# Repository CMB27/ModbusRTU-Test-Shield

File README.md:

# ModbusRTU Test Shield

A shield for Arduino boards that provides an RS-485 transceiver, RS-232 transceiver, and a selection of buttons, lights, and knobs.
This board was designed to aid in testing the [ModbusRTUSlave](https://github.com/CMB27/ModbusRTUSlave) and [ModbusRTUMaster](https://github.com/CMB27/ModbusRTUMaster) libraries.

- This shield is designed to work with both 5V and 3.3V Arduino boards.
- A 3-position removable screw terminal is used as the RS-485 interface.
- A RJ12 connector is used as the RS-232 inteface. The pinout of this connector is designed to make it compatible with Automation Direct products.
- The potentiomter knobs can be easily removed so you can stack other shields on top of this one.
- There is a switch to easily change between using a `HardwareSerial` port or a `SoftwareSerial` port.
- The selected serial port is connected to both the RS-485 and RS-232 transceivers, so not confugration changes are needed to switch between them.

> [!NOTE]
> This design is distributed WITHOUT ANY EXPRESS OR IMPLIED WARRANTY, INCLUDING OF MERCHANTABILITY, SATISFACTORY QUALITY AND FITNESS FOR A PARTICULAR PURPOSE.
> 
> This board is designed to use only one serial interface (RS-485 or RS-232) at a time.
> Attempting to use both at the same time is unlikely to damage the board, but could lead to unexpected behavior.

### Pinouts
#### Arduino Pin Usage
| Pin | Function              | pinMode                                           |
|-----|-----------------------|---------------------------------------------------|
| 0   | HardwareSerial RX     | INPUT (Set by HardwareSerial)                     |
| 1   | HardwareSerial TX     | OUTPUT (Set by HardwareSerial)                    |
| 2   | Button1 (BTN1)        | INPUT_PULLUP                                      |
| 3   | Button2 (BTN2)        | INPUT_PULLUP                                      |
| 5   | LED1 (L1)             | OUTPUT                                            |
| 6   | LED1 (L2)             | OUTPUT                                            |
| 7   | LED1 (L3)             | OUTPUT                                            |
| 8   | LED1 (L4)             | OUTPUT                                            |
| 10  | SoftwareSerial RX     | INPUT (Set by SoftwareSerial)                     |
| 11  | SoftwareSerial TX     | OUTPUT (Set by SoftwareSerial)                    |
| 13  | Driver Enable (DE)    | OUTPUT (set by ModbusRTUSlave or ModbusRTUMaster) |
| A0  | Potentiometer1 (POT1) | INPUT                                             |
| A1  | Potentiometer2 (POT2) | INPUT                                             |

_Unused Pins: 4, 9, 12, A2, A3, A4, A5_

#### RS-485 Interface (J5)
| Pin | Function  | Electrical Type |
|-----|-----------|-----------------|
| 1   | RS-485 D+ | Bidirectional   |
| 2   | RS-485 D- | Bidirectional   |
| 3   | GND       | Passive         |

#### RS-232 Interface (J6)
| Pin | Function  | Electrical Type |
|-----|-----------|-----------------|
| 1   | GND       | Passive         |
| 2   | 5V        | Power Output    |
| 3   | RS-232 RX | Input           |
| 4   | RS-232 TX | Output          |
| 5   | VBUS      | Power Input     |
| 6   | GND       | Passive         |

### Documentation
- [Schematic](ModbusRTU-Test-Shield.pdf)
- [KiCAD Source Files](src)
- [STEP 3D Model](extras/ModbusRTU-Test-Shield.step)

## Components

### Circuit Board
#### Specifications
- Board Length: __68.58mm__
- Board Width: __53.34mm__
- Board Thickness: __1.6mm__
- Substrate Material: __FR4__
- Copper Layers: __2__
- Copper Thickness: __1oz__
- Soldermask Color: __Any__ (Blue Suggested)
- Smallest Hole Diameter: __0.6mm__
- Smallest Trace Width: __0.2mm__ (7.8mil)
- Smallest Trace Spacing: __0.2mm__ (7.8mil)

#### Suppliers
Below are some circuit board manufacturers I have used in the past.
Generally you will need to upload the upload the [gerber and drill files](gerbers) to their websites in a .zip folder.

- [OSH Park](https://oshpark.com) is a US based circuit board fabrication service.
  They tend to be more expensive than other manufacturers and the number of options they give you are limited (If you use this manufacturer, I hope you like purple).

- [Seeed Studio Fusion](https://www.seeedstudio.com/fusion_pcb.html) makes circuit boards in China.
  They have a lot of options when ordering; please refer to the [specifications](#specifications) above when making your choices.
  They do have a circuit board assembly service as well, but I am not especially familiar with it.

### Purchase Components

| Reference    | Qty | Manufacturer           | Part Number           | Description                         | Notes                                                                                         |
|--------------|----:|------------------------|-----------------------|-------------------------------------|-----------------------------------------------------------------------------------------------|
| C1-C6        |   6 | KEMET                  | ESS105M050AB2EA       | 1uF Aluminum Electrolytic Capacitor |                                                                                               |
| D1-D4, D6-D8 |   7 | Würth Elektronik       | 151031YS06000         | Yellow LED                          |                                                                                               |
| D5           |   1 | Würth Elektronik       | 151031VS04000         | Green LED                           |                                                                                               |
| D9, D10      |   2 | Vishay                 | BAT43-TAP             | Schottky Diode                      |                                                                                               |
| D11          |   1 | Vishay                 | SB260S-E3/54          | Schottky Diode                      |                                                                                               |
| J1-J4        |   1 | SparkFun Electronics   | PRT-11417	            | Stacking Socket Header Kit          | This kit contains all the connectors for the Arduino interface.                               |
| J5           |   1 | Phoenix Contact        | 5434557               | 3-Position Terminal Block Plug      |                                                                                               |
| J6           |   1 | Amphenol ICC (FCI)     | 87180-066LF           | RJ12 Jack                           |                                                                                               |
| R1-R8        |   8 | Stackpole Electronics  | CFM14JT1K00           | 1K Ohm Resistor                     | These are generic 1K Ohm resistors; smilarly sized components of the same value should work.  |
| R9           |   1 | Stackpole Electronics  | CFM14JT10K0           | 10K Ohm Resistor                    | This is a generic 10K Ohm resistor; a smilarly sized component of the same value should work. |
| RV1, RV2     |   2 | Piher/Amphenol         | PT10MV10-103A2020-E-S | 10K Ohm Potentiometer               |                                                                                               |
| RV1, RV2     |   2 | Piher/Amphenol         | JPEPL6052INI          | Potentiometer Knob                  |                                                                                               |
| SW1-SW3      |   3 | Omron                  | B3F-1020              | 6mm Pushbutton Switch               | This is a generic 6mm pushbutton switch. Feel free to substitute.                             |
| SW4          |   1 | C&K                    | OS202011MS2QN1        | DPDT Slide Switch                   |                                                                                               |
| U1           |   1 | Texas Instruments      | SN65HVD3082EP         | RS-485 Half-Duplex Transceiver      |                                                                                               |
| U2           |   1 | Texas Instruments      | MAX232N               | RS-232 Transceiver                  |                                                                                               |
| XJ5          |   1 | Phoenix Contact        | 5430438               | 3-Position Terminal Block Header    |                                                                                               |
| XU1          |   1 | Assmann WSW Components | AR 08-HZL/01-TT       | 8-Position DIP Socket               |                                                                                               |
| XU2          |   1 | Assmann WSW Components | AR 16-HZL/01-TT       | 16-Position DIP Socket              |                                                                                               |

You may also want termination resistors for RS-485; 120 Ohms is a common value.

#### Suppliers
Below are some electronics suppliers I have used in the past:

- [Digi-Key](https://www.digikey.com/) is my usual go-to supplier for electronic components.
  Their website makes it pretty easy to sort through parts.

- [Mouser](https://www.mouser.com/) is very similar to Digi-Key in a lot of ways.
  They sometimes have better pricing, and they have excellent customer support.

- [Newark](https://www.newark.com/) tends to have a bit different selection than Digi-Key and Mouser, especially in the area of connectors.

- [Octopart](https://octopart.com/) is not a supplier per se; it is essenitally an electronic component search engine.
  This can be a very helpful tool when looking for parts, especially somewhat unusual ones, like extended socket headers.

All of these suppliers have a feature on their respective websites where you can upload a spreadsheet file, such as [ModbusRTU-Test-Shield-BOM.csv](ModbusRTU-Test-Shield-BOM.csv), to populate the cart or find parts.

## Assembly

### Tools and Supplies
| Item              | Optional | Notes                                                                                                                                              |
|-------------------|----------|----------------------------------------------------------------------------------------------------------------------------------------------------|
| Soldering Iron    | No       | Make sure you use a good quality soldering iron. A poor quality soldering iron will give you a miserable soldering experience.                     |
| Flush Cutters     | No       | These are used to trim component leads.                                                                                                            |
| Flux Core Solder  | No       | Leaded solder is easier to work with, but lead-free solder is better for the environment.                                                          |
| Solder Flux       | Yes      | Extra flux will make the solder flow better. I don't usually use it when through-hole soldering, but it can be helpful.                            |
| Solder Wick       | Yes      | This is used to remove solder from places you don't want it.                                                                                       |
| Solder Sucker     | Yes      | If you need to de-solder a component, this, along with solder wick, is the tool you want. This can quickly remove most of the solder from a joint. |
| Arduino Shield    | Yes      | This can be used to hold the stacking socket headers in place while being assembled.                                                               |
| Isopropyl Alcohol | Maybe    | This is used to remove flux. It is not needed if you are using no-clean flux.                                                                      |
| Dish Soap         | Maybe    | This is used to remove flux residue. It is not needed if you are using no-clean flux.                                                              |

**Note on Flux**  
Traditional flux if left on the assembled circuit board could cause some serious issues.
It can potentially cause shorts or significant [parasitic capacitance](https://en.wikipedia.org/wiki/Parasitic_capacitance).
It is also somewhat corrosive and can, over time, damage your circuit board.
This sort of flux must be cleaned off the board after assembly.  
To address these issues there are no-clean fluxes, that can be left on the circuit board assembly and are unlikly to cause these issues.
There are also water-soluble fluxes that can be cleaned off with hot water, though I have found that some isopropyl alcohol can speed up the process.
There are also fluxes that are both no-clean and water soluble; this is what I like to use.

### Assembly Steps
Except for the socketed parts, all the components are placed on the front side of the board and solderd on the back side of the board.
These steps go through soldering each component, starting with the shortest.  
The [interactive HTML BOM](https://github.com/CMB27/ModbusRTU-Test-Shield/blob/main/extras/ModbusRTU-Test-Shield-interactive-BOM.html) may be helpful to you in this process.
It graphically shows where each component goes on the board.
You will need to download it in order to view it; GitHub does not render HTML files in repositories.

<details><summary><strong>1. R1-R9 (Resistors) and D9-D11 (Diodes)</strong></summary>
  <blockquote>

Two different resistor values used.  
The 8 resistors furthest from the diode footprints (R1-R8) are 1K Ohm resistors.
The color code on these will be orange, orange, brown, gold.  
The resistor right next to the diode footprints (R9) is a 10K Ohm resistor.
The color code on this resistor will be brown, black, orange, gold.

Two different diode parts are used on this board.  
The smaller signal diodes (D9, D10) are placed next to the resistors.  
The larger power diode (D11) is placed right next to the RJ12 footprint.

- Bend the compnent leads so that the parts will fit in their footprints.
- Place the components.
- Bend the leads on the backside of the board to hold them in place.
- On the backside of the board, solder the leads to the pads.
- Trim the leads using the flush cutters.

  </blockquote>
</details>

<details><summary><strong>2. XU1-XU2 (Integrated Circuit Sockets)</strong></summary>
  <blockquote>

*You will likely need to install the sockets one at a time.*

- Place the socket so that the notch matches up with the notch shown on the circuit board.
- Flip the board over and solder two pins in opposite corners of the socket.
- Check that the socket is straight and seated correctly on the board.
  If everything looks good proceed, otherwise, reheat your solder joints one at a time and adjust the socket position.
- Solder the remaining pins.

  </blockquote>
</details>

<details><summary><strong>3. SW1-SW3 (Push-button Switches)</strong></summary>
  <blockquote>

- Place the switches; these have kinked leads, so they should stay once placed.
- Turn the board over and solder the leads to the board.

  </blockquote>
</details>

<details><summary><strong>4. D1-D8 (LEDs)</strong></summary>
  <blockquote>

The `ON` LED (D5), is green.  
All the other LEDs (D1-D4, D6-D8) are yellow.

- Place the LEDs in their respective footprints with the short lead (cathode) going through the squarish pad.
- Bend the leads on the backside of the board to hold them in place.
- Solder the leads.
- Trim the leads.

  </blockquote>
</details>

<details><summary><strong>5. RV1-RV2 (Potentiometers)</strong></summary>
  <blockquote>

*You will likely need to install the potentiometers one at a time.*

- Place the potentiometer.
- Flip the board over and solder the pins.

  </blockquote>
</details>

<details><summary><strong>6. XJ5 (Terminal Block Header)</strong></summary>
  <blockquote>

- Place the terminal block header.
- Solder one of the pins.
- Check the placement of the header; reheat the solder joint and make adjustments if necessary.
- Solder the remaining pins.

  </blockquote>
</details>

<details><summary><strong>7. C1-C6 (Capacitors)</strong></summary>
  <blockquote>

- Place the capacitors, ensuring the `-` symbol on the capacitors is facing away from the `+` symbol on the board.
  For capacitors, the positive lead goes through the squarish pad and the negative lead goes through the circular pad.
- Bend the leads on the backside of the board to hold the capacitors in place.
- Solder the leads.
- Trim the leads.

  </blockquote>
</details>

<details><summary><strong>8. J1-J4 (Arduino UNO Interface)</strong></summary>
  <blockquote>

- If you have a shield for the Arduino UNO, place the stacking socket headers on its pins, then place the socket header pins through the holes in the circuit board.
  This will make it easier and faster to install the sockets.
  If you don't have a shield you will likely need to install the sockets one at a time.
- Carefully flip the board over the board, holding the socket headers in place.
- Tack solder the end pins of each socket header.
- Check the placement of the headers and make adjustments as needed.
- Solder the remaining pins.
- If you used a shield, remove it now.

  </blockquote>
</details>

<details><summary><strong>9. SW4 (Slide Switch)</strong></summary>
  <blockquote>

- Place the slide switch.
- Flip the board over and solder two of the smaller pins in opposite corners.
- Check the placement of the switch, making adjustments as needed.
- Solder the remaining pins.

  </blockquote>
</details>

<details><summary><strong>10. J6 (RJ12 Jack)</strong></summary>
  <blockquote>

- Place the jack; it should snap in place.
- Flip the board over and solder all the pins.

  </blockquote>
</details>

<details><summary><strong>11. Clean Flux Off Board</strong></summary>
  <blockquote>

*If you used no-clean flux, you can skip this step.*

This step was written with water-soluble flux in mind.  
If you used non-water-soluble flux, you may need to use a different cleaning process.

- Use isopropyl alcohol with a toothbrush to remove the bulk of the flux.
- Clean the board with dish soap and warm water using the same toothbrush.
- Dry the board thoroughly. I like to use compressed air for this step.

  </blockquote>
</details>

<details><summary><strong>12. U1-U2 (Integrated Circuits)</strong></summary>
  <blockquote>

- Carefully bend the pins on the ICs so that they are straight up and down.
  I usually use a table surface to bend all the leads on one side of the chip at a time.
- Carefully instert the chips into the sockets on the board.
  Make sure you don't crumple any pins in this process.

  </blockquote>
</details>

<details><summary><strong>13. Finishing Touches</strong></summary>
  <blockquote>

- Insert the screw terminal block (J5) into its header.
- Insert the potentiometer knobs.

  </blockquote>
</details>

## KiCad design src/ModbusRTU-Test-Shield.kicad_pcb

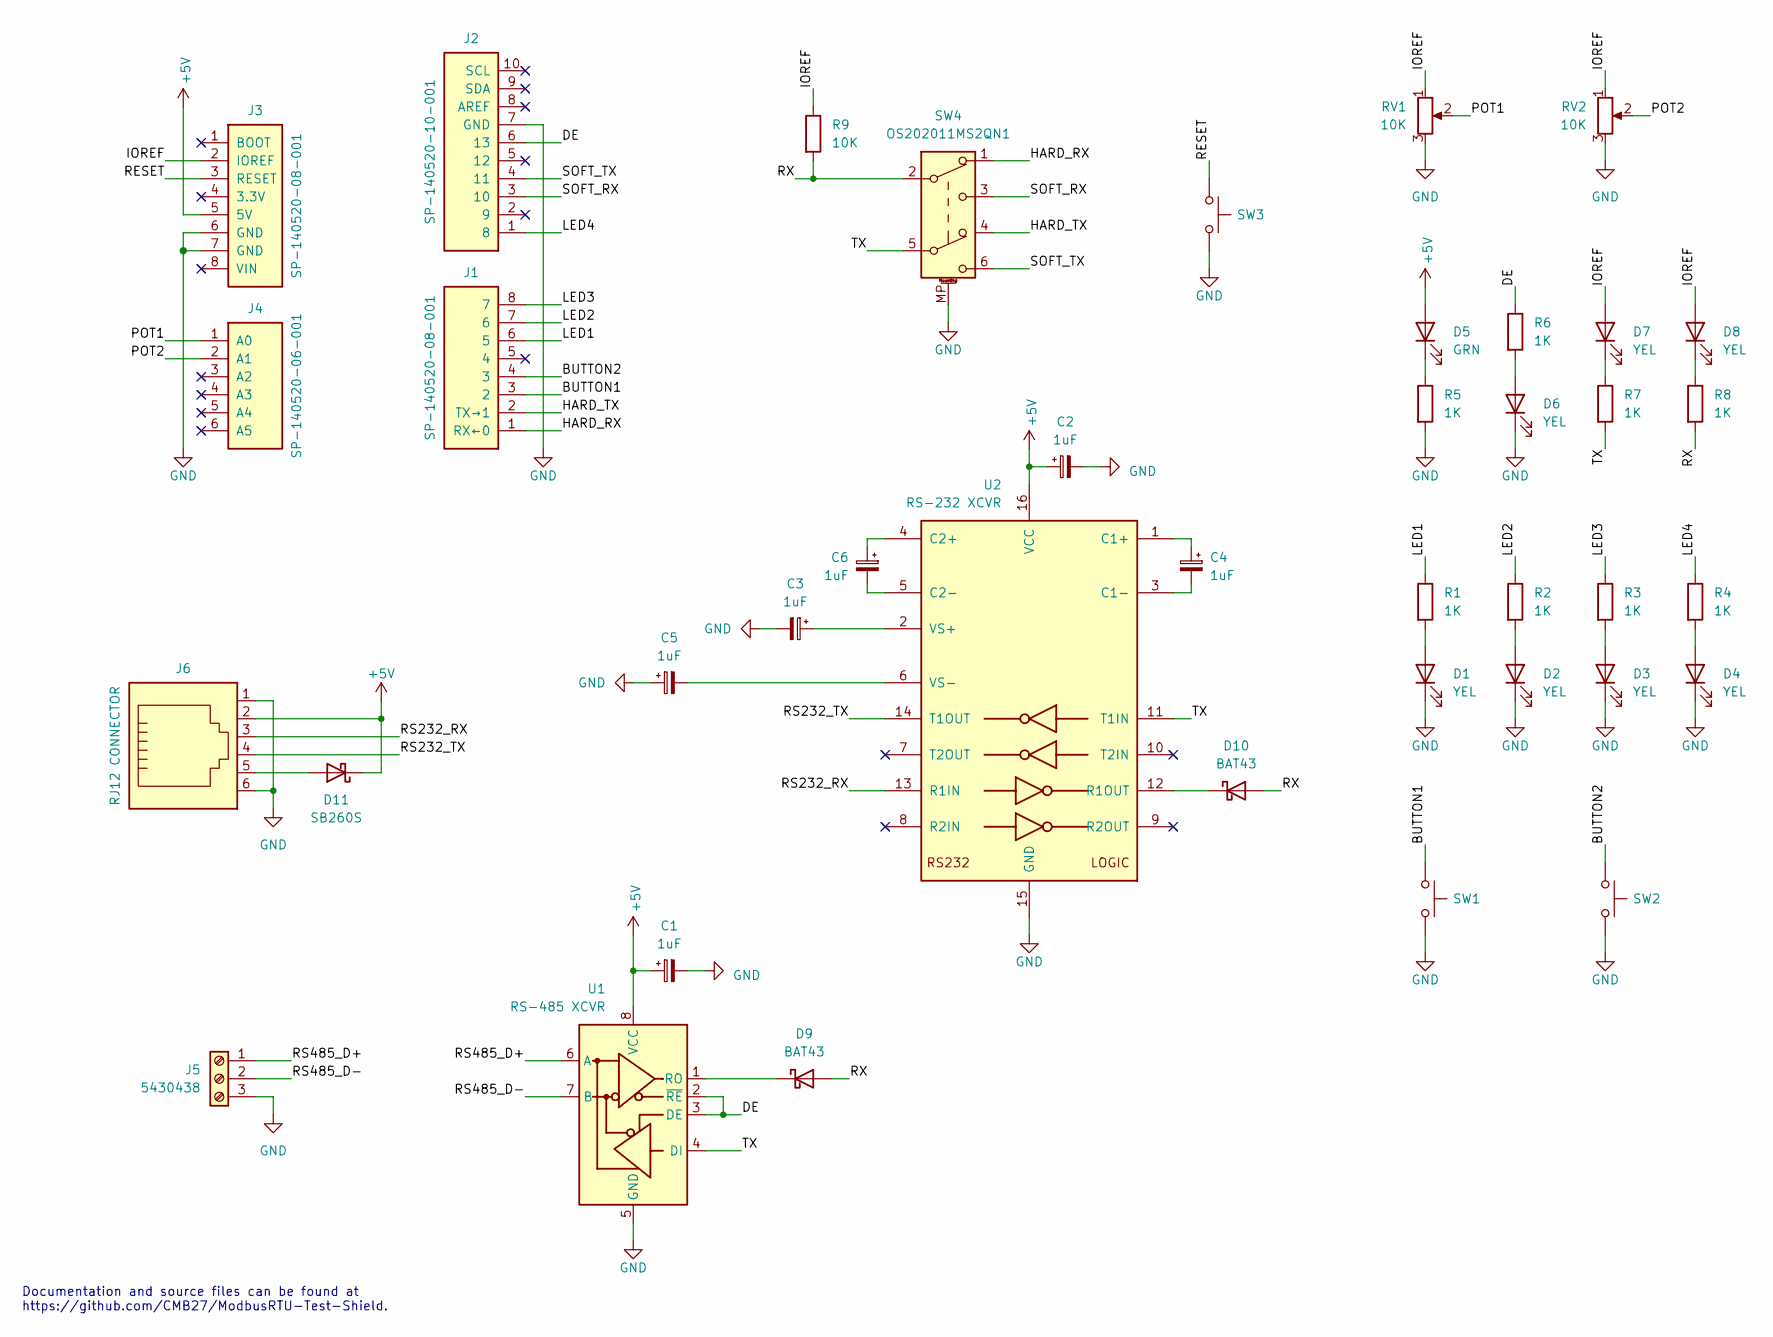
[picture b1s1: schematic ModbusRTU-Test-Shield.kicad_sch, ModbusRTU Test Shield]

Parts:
C1, C2, C3, C4, C5, C6: 1uF; CP_Radial_D4.0mm_P1.50mm; Part Number ESS105M050AB2EA
D1, D2, D3, D4, D6, D7, D8: YEL; LED_D3.0mm; Part Number 151031YS06000
D5: GRN; LED_D3.0mm; Part Number 151031VS04000
D9, D10: BAT43; D_DO-35_SOD27_P7.62mm_Horizontal; Part Number BAT43-TAP
D11: SB260S; D_DO-41_SOD81_P10.16mm_Horizontal; Part Number SB260S-E3/54
J1: SP-140520-08-001; PinSocket_1x08_P2.54mm_Vertical_UNO_Digital_1; Part Number SP-140520-08-001
J2: SP-140520-10-001; PinSocket_1x10_P2.54mm_Vertical_UNO_Digital_2; Part Number SP-140520-10-001
J3: SP-140520-08-001; PinSocket_1x08_P2.54mm_Vertical_UNO_Power; Part Number SP-140520-08-001
J4: SP-140520-06-001; PinSocket_1x06_P2.54mm_Vertical_UNO_Analog; Part Number SP-140520-06-001
J5: 5430438; PhoenixContact_BCH-350H-3_RS485; Part Number 5430438
J6: RJ12 CONNECTOR; FCI_54601-906WPLF; Part Number 87180-066LF
R1, R2, R3, R4, R5, R6, R7, R8: 1K; R_Axial_DIN0204_L3.6mm_D1.6mm_P7.62mm_Horizontal; Part Number CFM14JT1K00
R9: 10K; R_Axial_DIN0204_L3.6mm_D1.6mm_P7.62mm_Horizontal; Part Number CFM14JT10K0
RV1, RV2: 10K; Potentiometer_Piher_PT-10-V10_Vertical; Part Number PT10MV10-103A2020-E-S
SW1: BUTTON1; SW_PUSH_6mm; Part Number B3F-1020
SW2: BUTTON2; SW_PUSH_6mm; Part Number B3F-1020
SW3: RESET; SW_PUSH_6mm; Part Number B3F-1020
SW4: OS202011MS2QN1; SW_CK_OS202011MS2Qx1_DPDT; Part Number OS202011MS2QN1
U1: RS-485 XCVR; DIP-8_W7.62mm_Socket; Part Number SN65HVD3082EP
U2: RS-232 XCVR; DIP-16_W7.62mm_Socket; Part Number MAX232N

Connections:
+5V: C1.1, C2.1, D5.2 (A), D11.1 (K), J3.5 (5V), J6.2, U1.8 (VCC), U2.16 (VCC)
/BUTTON1: J1.3 (2), SW1.1
/BUTTON2: J1.4 (3), SW2.1
/DE: J2.6 (13), R6.1, U1.2 (~RE), U1.3 (DE)
/HARD_RX: J1.1 (RX←0), SW4.1 (A)
/HARD_TX: J1.2 (TX→1), SW4.4 (A)
/IOREF: D7.2 (A), D8.2 (A), J3.2 (IOREF), R9.1, RV1.1, RV2.1
/LED1: J1.6 (5), R1.1
/LED2: J1.7 (6), R2.1
/LED3: J1.8 (7), R3.1
/LED4: J2.1 (8), R4.1
/POT1: J4.1 (A0), RV1.2
/POT2: J4.2 (A1), RV2.2
/RESET: J3.3 (RESET), SW3.1
/RS232_RX: J6.3, U2.13 (R1IN)
/RS232_TX: J6.4, U2.14 (T1OUT)
/RS485_D+: J5.1, U1.6 (A)
/RS485_D-: J5.2, U1.7 (B)
/RX: D9.2 (A), D10.2 (A), R8.2, R9.2, SW4.2 (B)
/SOFT_RX: J2.3 (10), SW4.3 (C)
/SOFT_TX: J2.4 (11), SW4.6 (C)
/TX: R7.2, SW4.5 (B), U1.4 (DI), U2.11 (T1IN)
GND: C1.2, C2.2, C3.2, C5.1, D1.1 (K), D2.1 (K), D3.1 (K), D4.1 (K), D6.1 (K), J2.7 (GND), J3.6 (GND), J3.7 (GND), J5.3, J6.1, J6.6, R5.2, RV1.3, RV2.3, SW1.2, SW2.2, SW3.2, SW4.MP (MountPin), U1.5 (GND), U2.15 (GND)
unnamed: D1.2 (A), R1.2
unnamed: D2.2 (A), R2.2
unnamed: D3.2 (A), R3.2
unnamed: D4.2 (A), R4.2
unnamed: D5.1 (K), R5.1
unnamed: D6.2 (A), R6.2
unnamed: D7.1 (K), R7.1
unnamed: D8.1 (K), R8.1
unnamed: D9.1 (K), U1.1 (RO)
unnamed: D10.1 (K), U2.12 (R1OUT)
unnamed: D11.2 (A), J6.5
unnamed: C4.1, U2.1 (C1+)
unnamed: C4.2, U2.3 (C1-)
unnamed: C6.1, U2.4 (C2+)
unnamed: C6.2, U2.5 (C2-)
unnamed: C3.1, U2.2 (VS+)
unnamed: C5.2, U2.6 (VS-)

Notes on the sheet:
Documentation and source files can be found at https://github.com/CMB27/ModbusRTU-Test-Shield.

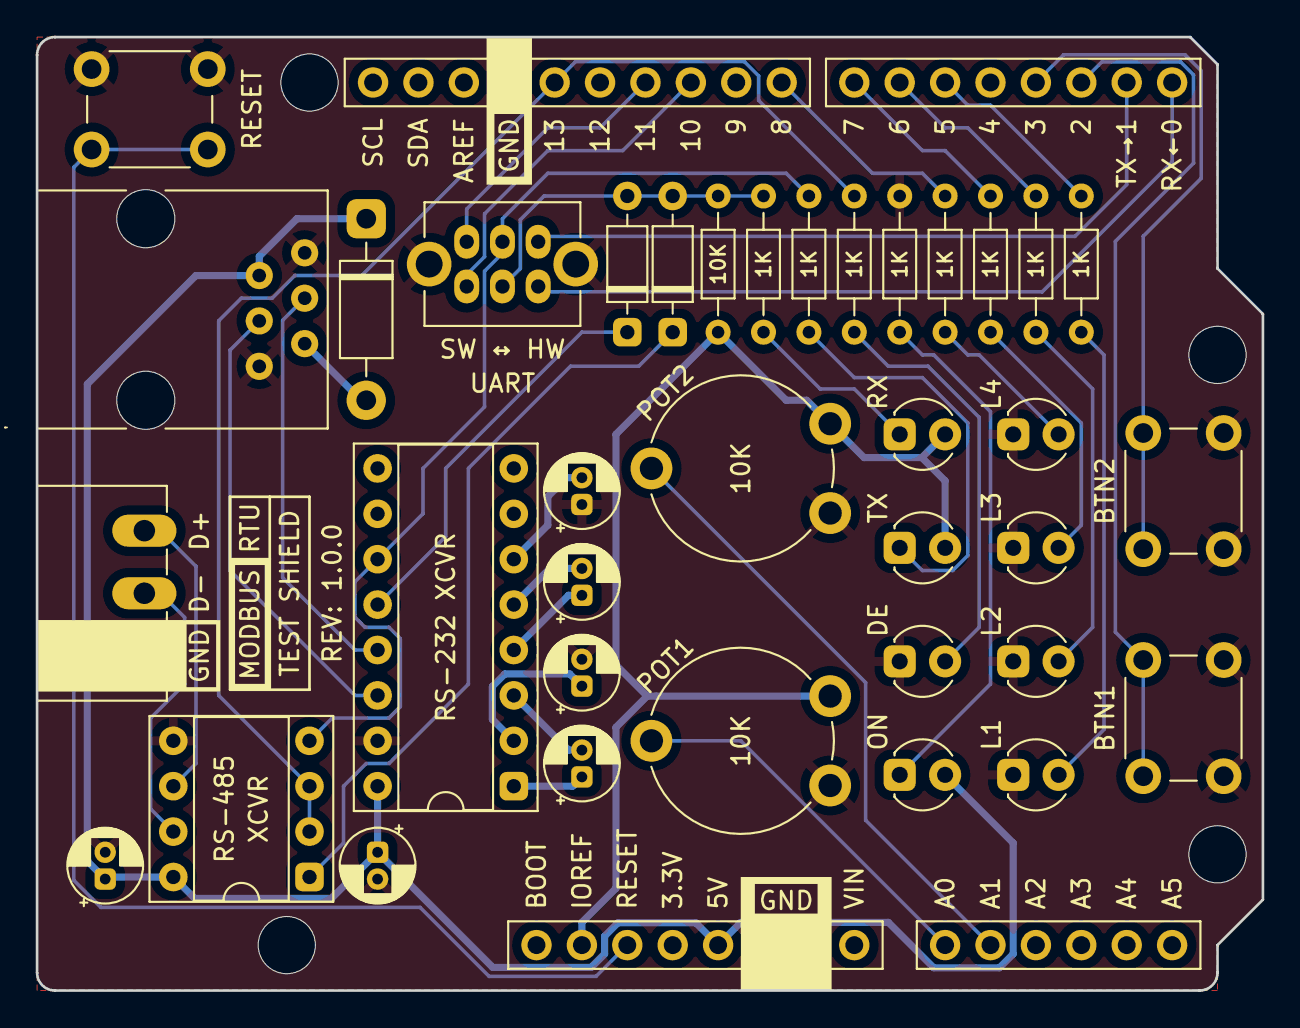
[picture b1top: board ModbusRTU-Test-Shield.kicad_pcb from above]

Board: 2 copper layers, 68.6 x 53.3 mm, 44 parts (0 on the bottom side), 40 nets.

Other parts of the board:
MH1, MH2, MH3, MH4: MountingHole_3.2mm

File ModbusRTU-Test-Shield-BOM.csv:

Reference,Qty,Manufacturer,Part Number,Description
,1,,,ModbusRTU Test Shield Bare Circuit Board
C1-C6,6,KEMET,ESS105M050AB2EA,1uF Aluminum Electrolytic Capacitor
"D1-D4, D6-D8",7,Würth Elektronik,151031YS06000,Yellow LED
D5,1,Würth Elektronik,151031VS04000,Green LED
"D9, D10",2,Vishay,BAT43-TAP,Schottky Diode
D11,1,Vishay,SB260S-E3/54,Schottky Diode
J1-J4,1,SparkFun Electronics,PRT-11417,Stacking Socket Header Kit
J5,1,Phoenix Contact,5434557,3-Position Terminal Block Plug
J6,1,Amphenol ICC (FCI),87180-066LF,RJ12 Connector
R1-R8,8,Stackpole Electronics,CFM14JT1K00,1K Ohm Resistor
R9,1,Stackpole Electronics,CFM14JT10K0,10K Ohm Resistor
"RV1, RV2",2,Piher/Amphenol,PT10MV10-103A2020-E-S,10K Ohm Potentiometer
"RV1, RV2",2,Piher/Amphenol,JPEPL6052INI,Potentiometer Knob
SW1-SW3,3,Omron,B3F-1020,6mm Pushbutton Switch
SW4,1,Amphenol ICC (FCI),OS202011MS2QN1,DPDT Slide Switch
U1,1,Texas Instruments,SN65HVD3082EP,RS-485 Half-Duplex Transceiver
U2,1,Texas Instruments,MAX232N,RS-232 Transceiver
XJ5,1,Phoenix Contact,5430438,3-Position Terminal Block Header
XU1,1,Assmann WSW Components,AR 08-HZL/01-TT,8-Position DIP Socket
XU2,1,Assmann WSW Components,AR 16-HZL/01-TT,16-Position DIP Socket

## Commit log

2023-12-10 Started circuit board layout.
2023-12-10 Completed first draft.
2023-12-11 Added RS-232 on an RJ12 connector. Completed second draft.
2023-12-14 Added some 3D models. Created project footprints for RJ12 and screw terminal connectors. Placed and locked RJ12 and screw terminal connector.
2023-12-16 Refined button footprints. Updated and refined potentiometer footprints and models.
2023-12-17 Added model and footprint for DPDT slide switch.
2023-12-17 Consolidated all the 3D model .txt notes into one file.
2023-12-17 Changed the 3D model used for the socket/header of the screw terminal.
2023-12-17 Updated the schematic and board to use the new footprints and models.
2023-12-17 Removed the unused models and footprints from project_libraries.
2023-12-19 Completed third draft.
2023-12-22 Completed fourth draft.
2023-12-26 Created a 3D model of the capacitor.
2023-12-26 Copied the used 3D models from the KiCad library into project_libraries/Project_3DModels.3dshapes. Updated Project_3DModels_notes.
2023-12-26 Put all of the used symbols into project_libraries/Project_Symbols.kicad_sym.
2023-12-26 Updated project_libraries/Project_Footprints.pretty.
2023-12-26 Updated the main source files.
2023-12-26 Updated the source files.
2023-12-26 Generated gerber and drill files.
2023-12-26 Generated some renderings of the circuit board assembly.
2023-12-26 Generated a 3D model of the circuit board assembly.
2023-12-26 Generated an interactive html BOM.
2023-12-26 Generated a PDF of the schematic.
2023-12-26 Created the BOM.
2023-12-26 Updated src/.gitignore to ignore interactive BOM generation settings files.
2023-12-26 Added more detail to README.
2023-12-26 Update README.md
    Fixed a spelling error.
2023-12-26 Added the revision number to the schematic.
2023-12-27 Created and tested production_file_creation_steps.
2023-12-27 Improved the placement of a value and reference in the schematic.
2023-12-28 Made several cosmetic improvements to the schematic and board. Changed the revision from 0.0.1 to 0.0.2.
2023-12-28 Moved the production file creation steps markdown file from src to extras. Added images to the instructions. Tweaked the instructions based on some differences in Windows.
2023-12-28 Update README.md
    Added Tools and Supplies sub-section to Assembly section.
2023-12-29 Update README.md
    Added assembly steps.
2023-12-29 Updated README.
2024-01-06 Made some changes based on build.
2024-11-29 Updated board to 1.0.0. Changed out RJ12 connector for one that is not obsolete. Changed out RS-485 tranceiver for a less expensive model.

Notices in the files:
src/ModbusRTU-Test-Shield.kicad_pcb:
© 2023 C. M. Bulliner. Released under the CERN-OHL-P v2 license.
LICENSED UNDER CERN-OHL-P V2
